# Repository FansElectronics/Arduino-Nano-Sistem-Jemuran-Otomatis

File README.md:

# Arduino-Nano-Sistem-Jemuran-Otomatis
ARDUINO PROJECT: SISTEM JEMURAN OTOMATIS DENGAN SENSOR HUJAN DAN CAHAYA
Baca Lengkap disini : https://www.fanselectronics.com/2019/01/10/arduino-project-sistem-jemuran-otomatis-dengan-sensor-hujan-dan-cahaya/

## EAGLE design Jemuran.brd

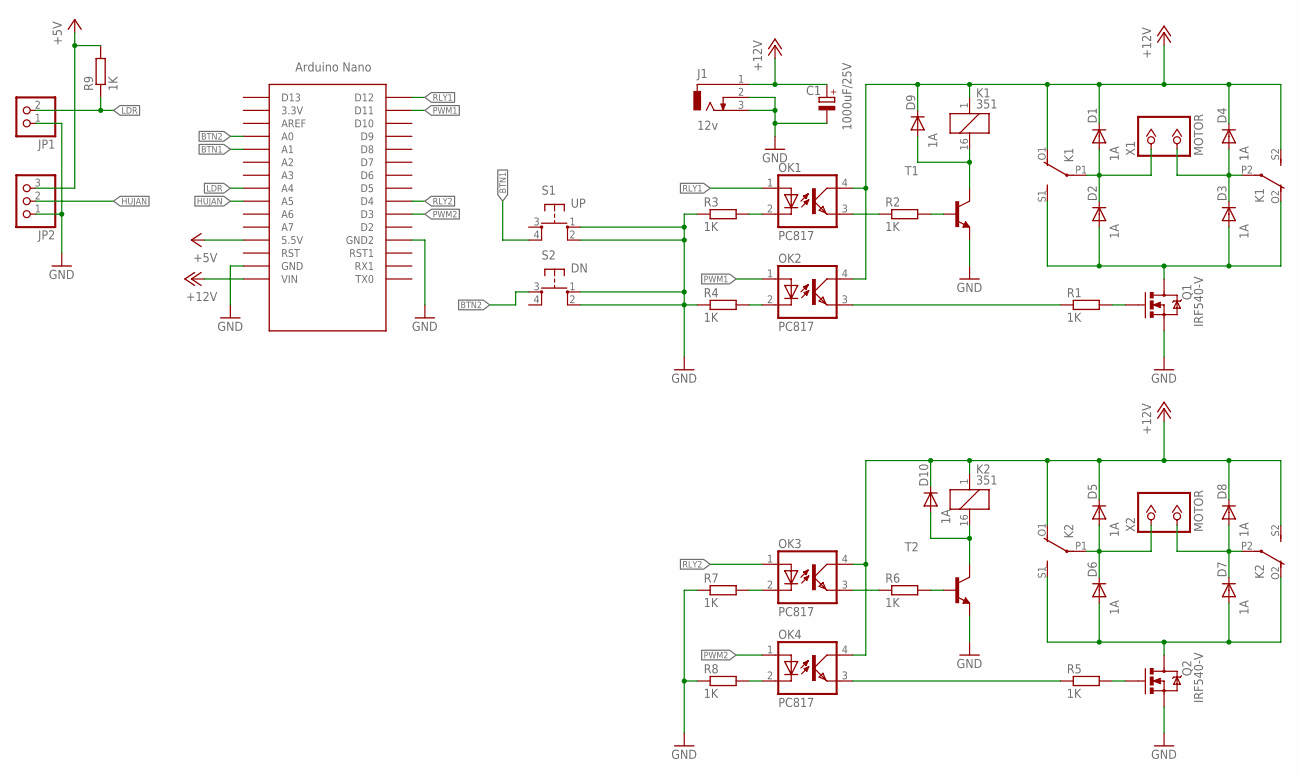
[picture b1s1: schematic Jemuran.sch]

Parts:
C1: 1000uF/25V; E3,5-10
D1, D2, D3, D4, D5, D6, D7, D8, D9, D10: 1A; D40-10
J1: 12v; JACK-PCB-ARDUINO
JP1: PINHD-1X2; 1X02
JP2: PINHD-1X3; 1X03
K1, K2: 351
OK1, OK2, OK3, OK4: PC817; DIL04
Q1, Q2: IRF540-V; TO220V
R1, R2, R3, R4, R5, R6, R7, R8, R9: 1K; 0207/7
S1: UP; TACT-6X6MM-OCTAGON
S2: DN; TACT-6X6MM-OCTAGON
T1, T2: -NPN-TO92-EBC; TO92-EBC
U$1: NANO
X1, X2: MOTOR; KL2

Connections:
+5V: JP2.3, R9.2, U$1.5V (5.5V)
+12V: C1.+, D1.C, D4.C, D5.C, D8.C, D9.C, D10.C, J1.1, K1.1, K1.O1 (O), K1.S2 (S), K2.1, K2.O1 (O), K2.S2 (S), OK1.4 (COL), OK2.4 (COL), OK3.4 (COL), OK4.4 (COL), U$1.VIN
BTN1: S1.4 (P1), U$1.A1
BTN2: S2.3, U$1.A0
GND: C1.-, J1.2, J1.3, JP1.1, JP2.1, Q1.3 (S), Q2.3 (S), R3.1, R4.1, R7.1, R8.1, S1.1 (S), S1.2 (S1), S2.1 (S), S2.2 (S1), T1.E, T2.E, U$1.GND, U$1.GND1 (GND2)
HUJAN: JP2.2, U$1.A5
LDR: JP1.2, R9.1, U$1.A4
unnamed: Q1.1 (G), R1.2
unnamed: D2.A, D3.A, K1.O2 (O), K1.S1 (S), Q1.2 (D)
unnamed: D1.A, D2.C, K1.P1, X1.1
unnamed: D3.C, D4.A, K1.P2, X1.2
unnamed: OK2.3 (EMIT), R1.1
unnamed: D9.A, K1.16 (2), T1.C
unnamed: R2.2, T1.B
unnamed: OK1.2 (C), R3.2
unnamed: OK1.3 (EMIT), R2.1
unnamed: OK2.2 (C), R4.2
unnamed: D6.A, D7.A, K2.O2 (O), K2.S1 (S), Q2.2 (D)
unnamed: D5.A, D6.C, K2.P1, X2.1
unnamed: D7.C, D8.A, K2.P2, X2.2
unnamed: Q2.1 (G), R5.2
unnamed: OK4.3 (EMIT), R5.1
unnamed: D10.A, K2.16 (2), T2.C
unnamed: R6.2, T2.B
unnamed: OK3.3 (EMIT), R6.1
unnamed: OK3.2 (C), R7.2
unnamed: OK4.2 (C), R8.2
PWM1: OK2.1 (A), U$1.D11
PWM2: OK4.1 (A), U$1.D3
RLY1: OK1.1 (A), U$1.D12
RLY2: OK3.1 (A), U$1.D4

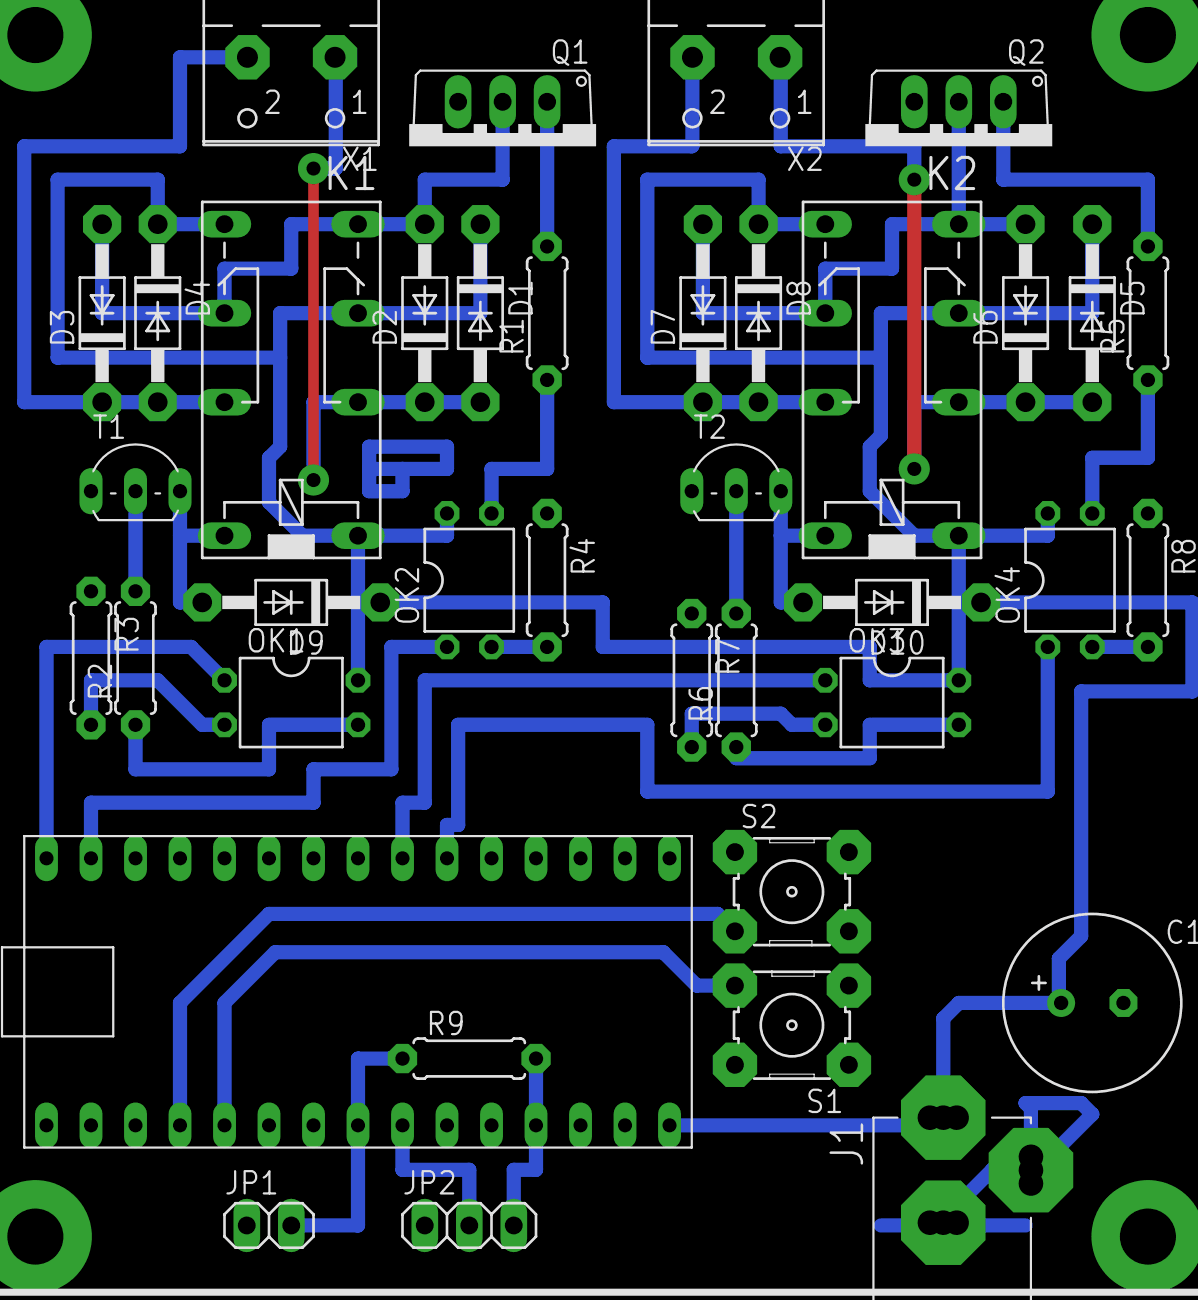
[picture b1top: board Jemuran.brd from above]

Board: 2 copper layers, 38 parts (0 on the bottom side), 31 nets.

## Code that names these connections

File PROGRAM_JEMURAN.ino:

//==================================================
#include <EEPROM.h>                                 // Library EEPROM

// Definisikan PIN, agar lebih mudah
#define WATER        A5
#define LDR          A4
#define BUP          A0
#define BDN          A1
#define RLY1         4
#define RLY2         12
#define PWM1         3
#define PWM2         11

#define delayMotor   1000    // Delay 1000 ms untuk nyala motor
#define batasCahaya  30      // Batas persentase Data Cahaya < 30 = Mendung
#define batasHujan   30      // Batas persentase Data Cahaya > 30 = Hujan

#define TUTUP        0
#define BUKA         1


// Deklarasi Variable
int hujan, cahaya, spd, jemuran;
int  toleransi   = 2;             // Toleransi untuk jaga-jaga naik turunya data terlalu cepat.
byte speedMotor  = 100;           // kecepatan awal motor, jika tidak disimpan di EEPROM
String stats;                     // Status Serial Debug     
//==================================================
void setup() {
  Serial.begin(9600);       // Aktifkan Serial Monitoring

  // Ubah mode PIN
  pinMode(BUP, INPUT_PULLUP);
  pinMode(BDN, INPUT_PULLUP);
  pinMode(RLY1, OUTPUT);
  pinMode(RLY2, OUTPUT);
  pinMode(PWM1, OUTPUT);
  pinMode(PWM2, OUTPUT);
}

//==================================================
void loop() {
  speedMotor = 255;
  cahaya     = 20;
  hujan      = 30;
  spd        = map(speedMotor, 0, 255, 0, 100);                 // 0 s/d 100  persen

  DEBUG();

  if (digitalRead(BUP) == LOW) speedMotor++;                // Tombol + Kecepatan Motor
  if (digitalRead(BDN) == LOW) speedMotor--;                // Tombol - Kecepatan Motor
  EEPROM.write(0, speedMotor);

  // Kondisi CAHAYA = Mendung / Malam dan HUJAN = BASAH
  if (cahaya < (batasCahaya - toleransi) and hujan > (batasHujan + toleransi) and jemuran == BUKA) {
    motorTutup();
    stats = "TUTUP, MENDUNG, BASAH";
  }
  // Kondisi CAHAYA = Siang dan HUJAN = BASAH
  else if (cahaya > (batasCahaya + toleransi) and hujan > (batasHujan + toleransi) and jemuran == BUKA) {
    motorTutup();
    stats = "TUTUP, SIANG, BASAH";
  }
  // Kondisi CAHAYA = Mendung dan HUJAN = KERING
  else if (cahaya < (batasCahaya - toleransi) and hujan < (batasHujan - toleransi) and jemuran == BUKA) {
    motorTutup();
    stats = "TUTUP, MENDUNG, KERING";
  }
  // Kondisi CAHAYA = Siang dan HUJAN = KERING
  else if (cahaya > (batasCahaya + toleransi) and hujan < (batasHujan - toleransi) and jemuran == TUTUP) {
    motorBuka();
    stats = "BUKA, SIANG, KERING";
  }
  delay(100);
}

//==================================================
void DEBUG() {
  Serial.print("CAHAYA : ");
  Serial.print(cahaya);
  Serial.print(" %   , ");
  Serial.print("HUJAN : ");
  Serial.print(hujan);
  Serial.print(" %   , ");
  Serial.print("SPEED : ");
  Serial.print(spd);
  Serial.print(" %   , ");
  Serial.print("STATUS : ");
  Serial.println(stats);
}

//==================================================
void motorBuka() {
  digitalWrite(RLY1, BUKA);            // Relay Aktif = Arah motor Buka
  digitalWrite(RLY2, BUKA);
  analogWrite(PWM1, speedMotor);       // Sinyal PWM untuk kecepatan motor
  analogWrite(PWM2, speedMotor);
  delay(delayMotor);                   // Jeda motor untuk menyala sampai jemuran terbuka
  digitalWrite(RLY1, LOW);             // Matikan Relay
  digitalWrite(RLY2, LOW);
  analogWrite(PWM1, 0);                // Matikan Sinyal PWM = Motor Berhenti
  analogWrite(PWM2, 0);
  jemuran = BUKA;
}

//==================================================
void motorTutup() {
  digitalWrite(RLY1, TUTUP);            // Relay Mati = Arah motor TUTUP
  digitalWrite(RLY2, TUTUP);
  analogWrite(PWM1, speedMotor);       // Sinyal PWM untuk kecepatan motor
  analogWrite(PWM2, speedMotor);
  delay(delayMotor);                   // Jeda motor untuk menyala sampai jemuran terbuka
  digitalWrite(RLY1, LOW);             // Matikan Relay
  digitalWrite(RLY2, LOW);
  analogWrite(PWM1, 0);                // Matikan Sinyal PWM = Motor Berhenti
  analogWrite(PWM2, 0);
  jemuran = TUTUP;
}
